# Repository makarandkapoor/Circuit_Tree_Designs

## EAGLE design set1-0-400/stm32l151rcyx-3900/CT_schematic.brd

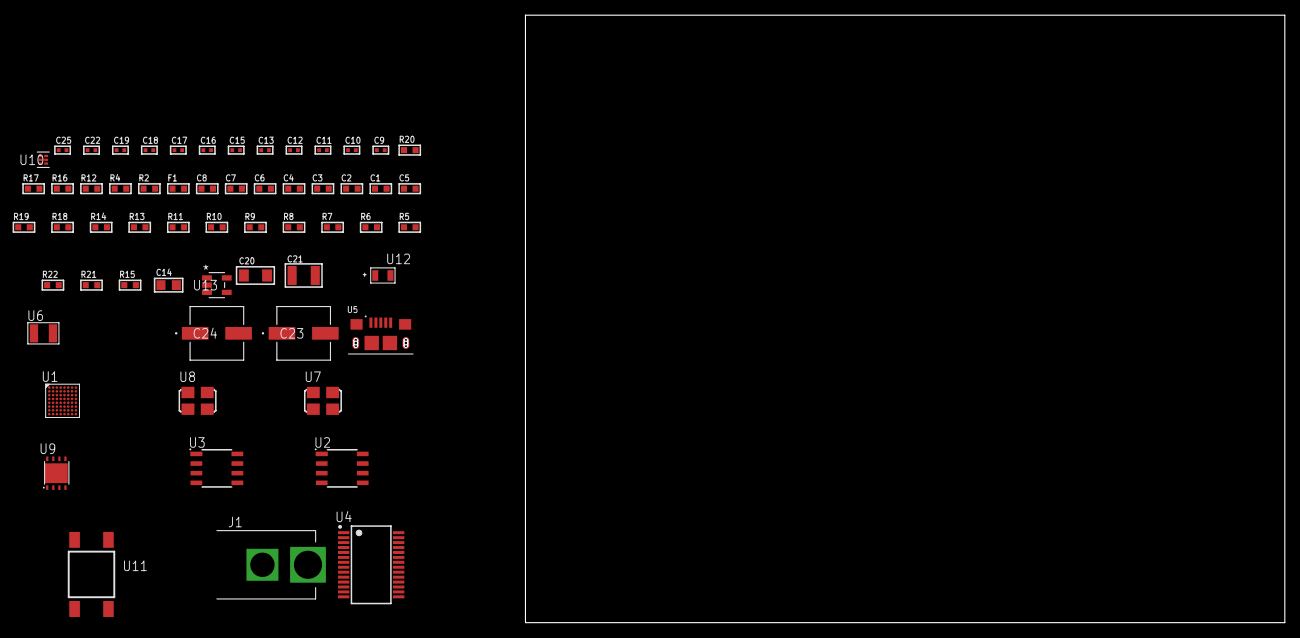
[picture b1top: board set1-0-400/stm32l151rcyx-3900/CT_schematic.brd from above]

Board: 2 copper layers, 122.6 x 80.0 mm, 60 parts (0 on the bottom side), 41 nets, no tracks yet.

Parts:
C1, C2, C3, C4, C6: 1e-07; C0603
C5: 4.7e-06; C0603
C7: 1e-08; C0603
C8: 1e-06; C0603
C9, C10: 1e-11; C0402
C11, C12, C17, C18, C19, C25: 1e-08; C0402
C13, C15, C16, C22: 1e-07; C0402
C14: 4.7e-06; C0805
C20: 1e-05; C1206
C21: 1e-05; C1210
C23, C24: 0.0001; EXV-9H
F1: 240.0; L0603
J1: PJ-037B; PJ-037B_PACKAGE
R2, R17: 1000.0; R0603
R4, R12: 4700.0; R0603
R5, R6, R7, R8, R9, R10, R11, R13, R14, R18, R19: 10000.0; R0603
R15: 100000.0; R0603
R16: 2231.0; R0603
R20: 9100.0; R0603
R21: 680000.0; R0603
R22: 120000.0; R0603
U1: STM32L151RCY6TR; WLCSP64
U2, U3: AT25020B-SSHL-T; SOIC-8
U4: FT232RL-REEL; SSOP-28
U5: 10118193-0001LF; FCI_10118193-0001LF
U6: ABS07-32.768KHZ-7-T
U7: ASFL1-12MHZ-NCS; ASFL1
U8: ASFL1-25MHZ-NCS; ASFL1
U9: LP3878SDX-ADJ/NOPB; WSON-8
U10: TPS3895ADRYR; SON-6
U11: 4-1437565-2; SW_4-1437565-2
U12: Q65110A2395; LGM67K-G1J2-24-Z
U13: nc7sz125m5x; NC7SZ125M5X

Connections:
CLK_CRYSTAL_U1_B7: C9.1, U1.B7, U6.1
CLK_CRYSTAL_U1_B8: C10.1, U1.B8, U6.2
CLK_U1_D8: U1.D8, U8.3
CLK_U4_27: U4.27, U7.3
GND: C1.2, C2.2, C3.2, C4.2, C5.2, C6.2, C7.2, C8.2, C9.2, C10.2, C11.2, C12.2, C13.2, C14.2, C15.2, C16.2, C17.2, C18.2, C19.2, C20.2, C21.2, C22.2, C23.2, C24.2, C25.2, J1.2, R2.2, R5.2, R14.2, R17.2, R20.2, R22.2, U1.A7, U1.B1, U1.E7, U1.F5, U1.H2, U2.4, U3.4, U4.7, U4.18, U4.21, U4.25, U4.26, U5.5, U5.6, U5.7, U5.8, U5.9, U7.2, U8.2, U9.3, U9.PAD, U10.2, U12.C, U13.1, U13.3
NET_U1_A6: R5.1, U1.A6
NET_U1_C6: C6.1, U1.C6
NET_U1_C7: R4.1, U1.C7, U13.4
NET_U1_G8: C7.1, C8.1, F1.1, U1.G8
NET_U1_H8: U11.3, U11.4
NET_U2_3: R6.1, U2.3
NET_U2_7: R8.1, U2.7
NET_U3_3: R9.1, U3.3
NET_U3_7: R11.1, U3.7
NET_U4_14: R13.1, U4.14
NET_U4_17: C15.1, U4.17
NET_U4_19: R14.1, U4.19
NET_U5_1: R12.1, U5.1
NET_U5_2: U4.16, U5.2
NET_U5_3: U4.15, U5.3
NET_U9_1: C19.1, U9.1
NET_U9_6: R16.2, R17.1, U9.6
NET_U9_8: R15.1, U9.8
NET_U10_1: R19.1, R20.1, U10.1
NET_U10_3: R21.2, R22.1, U10.3
NET_U10_4: R18.1, U10.4, U13.2
NET_U11_1: R2.1, U11.1, U11.2
PROC_SPI1_MISO: U1.B4, U2.2
PROC_SPI1_MOSI: U1.A5, U2.5
PROC_SPI1_NSS: R7.1, U1.C3, U2.1
PROC_SPI1_SCK: U1.A4, U2.6
PROC_SPI2_MISO: U1.F2, U3.2
PROC_SPI2_MOSI: U1.F1, U3.5
PROC_SPI2_NSS: R10.1, U1.G2, U3.1
PROC_SPI2_SCK: U1.G1, U3.6
PROC_USART1_CTS: U1.C1, U4.3
PROC_USART1_RTS: U1.C2, U4.11
PROC_USART1_RX: U1.C5, U4.1
PROC_USART1_TX: U1.B5, U4.5
VCC_S1_6V3: C20.1, C23.1, C24.1, J1.1, R15.2, U9.4
VCC_TIER1_3V3: C1.1, C2.1, C3.1, C4.1, C5.1, C11.1, C12.1, C13.1, C14.1, C16.1, C17.1, C18.1, C21.1, C22.1, C25.1, F1.2, R4.2, R6.2, R7.2, R8.2, R9.2, R10.2, R11.2, R13.2, R16.1, R18.2, R19.2, R21.1, U1.A1, U1.A8, U1.G6, U1.H1, U2.8, U3.8, U4.4, U4.20, U7.4, U8.4, U9.5, U10.6, U13.5

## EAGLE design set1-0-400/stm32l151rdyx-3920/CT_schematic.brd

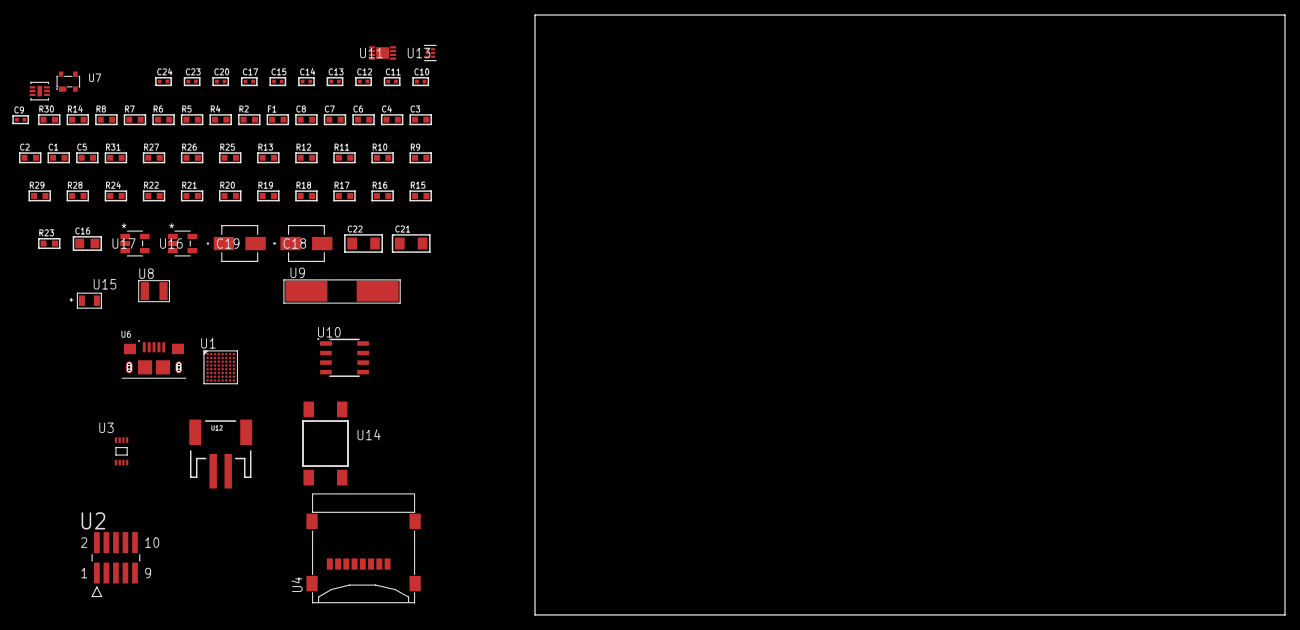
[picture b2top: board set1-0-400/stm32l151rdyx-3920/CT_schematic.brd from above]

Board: 2 copper layers, 71 parts (0 on the bottom side), 40 nets, no tracks yet.

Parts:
C1, C2, C3, C4, C6: 1e-07; C0603
C5: 4.7e-06; C0603
C7: 1e-08; C0603
C8: 1e-06; C0603
C9, C10, C11, C12: 1e-11; C0402
C13, C15, C17, C20: 1e-07; C0402
C14, C23, C24: 1e-08; C0402
C16: 1e-05; C0805
C18: 1e-06; EXV-9B
C19: 2.2e-06; EXV-9B
C21, C22: 1e-05; C1206
F1: 240.0; L0603
R2: 1000.0; R0603
R4: 4700.0; R0603
R5, R6, R7, R8: 2200.0; R0603
R9, R10, R11, R12, R13, R25, R26, R31: 10000.0; R0603
R14: 5.0; R0603
R15, R16, R17, R18, R19, R20, R21, R22, R24: 100000.0; R0603
R23: 101022.32; R0603
R27: 18000.0; R0603
R28: 470000.0; R0603
R29: 120000.0; R0603
R30: 2000.0; R0603
U1: STM32L151RDY6; WLCSP64
U2: FTSH-105-01-L-DV-K; SAMTEC_FTSH-105-01-L-DV-K
U3: 24AA04-I/MC; TDFN-8/6MM
U4: 0472192001; MOLEX_47219-2001
U5: SI7006-A20-IM; DFN-6
U6: 10118193-0001LF; FCI_10118193-0001LF
U7: prtr5v0u2ax; SOT143B
U8: ABS07-32.768KHZ-7-T
U9: ABLS-25.000MHZ-B2F-T
U10: LP2954AIMX/NOPB; LP2954
U11: MCP73831T-2ACI/MC; DFN8_2X3MC
U12: S2B-PH-SM4-TB(LF)(SN); JST-2-SMD
U13: TPS3895ADRYR; SON-6
U14: 4-1437565-2; SW_4-1437565-2
U15: Q65110A2395; LGM67K-G1J2-24-Z
U16, U17: nc7sz125m5x; NC7SZ125M5X

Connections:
CLK_CRYSTAL_U1_B7: C9.1, U1.B7, U8.1
CLK_CRYSTAL_U1_B8: C10.1, U1.B8, U8.2
CLK_CRYSTAL_U1_D7: C11.1, U1.D7, U9.1
CLK_CRYSTAL_U1_D8: C12.1, U1.D8, U9.2
GND: C1.2, C2.2, C3.2, C4.2, C5.2, C6.2, C7.2, C8.2, C9.2, C10.2, C11.2, C12.2, C13.2, C14.2, C15.2, C16.2, C17.2, C18.2, C19.2, C20.2, C21.2, C22.2, C23.2, C24.2, R2.2, R9.2, R13.2, R14.2, R24.2, R27.2, R29.2, R30.2, U1.A7, U1.B1, U1.E7, U1.F5, U1.H2, U2.3, U2.5, U3.4, U3.7, U4.6, U4.G1, U4.G2, U4.G3, U4.G4, U5.2, U5.7, U6.5, U6.6, U6.7, U6.8, U6.9, U7.1, U10.4, U11.6, U11.9, U12.2, U13.2, U15.C, U16.2, U16.3, U17.1, U17.3
INPUT_USBPOWER_5V: C21.1, R31.2, U6.1, U7.4, U11.1, U11.2
NET_U1_A6: R9.1, U1.A6
NET_U1_B5: R5.1, U1.B5, U5.6
NET_U1_B6: R6.1, U1.B6, U5.1
NET_U1_C6: C6.1, U1.C6
NET_U1_C7: R4.1, U1.C7, U17.4
NET_U1_F3: R8.1, U1.F3, U3.5
NET_U1_G3: R7.1, U1.G3, U3.6
NET_U1_G8: C7.1, C8.1, F1.1, U1.G8
NET_U1_H8: U14.3, U14.4
NET_U2_9: R14.1, U2.9
NET_U10_3: R22.1, U10.3
NET_U10_5: R21.1, U10.5
NET_U10_7: R23.2, R24.1, U10.7
NET_U11_5: R31.1, U11.5
NET_U11_8: R30.1, U11.8
NET_U13_1: R26.1, R27.1, U13.1
NET_U13_3: R28.2, R29.1, U13.3
NET_U13_4: R25.1, U13.4, U16.4, U17.2
NET_U14_1: R2.1, U14.1, U14.2
PROC_SDIO_CK: R16.1, U1.C4, U4.5
PROC_SDIO_CMD: R15.1, U1.A3, U4.3
PROC_SDIO_D0: R17.1, U1.E3, U4.7
PROC_SDIO_D1: R18.1, U1.D1, U4.8
PROC_SDIO_D2: R19.1, U1.A2, U4.1
PROC_SDIO_D3: R20.1, U1.B3, U4.2
PROC_SYS_JTCK_SWCLK: R13.1, U1.B2, U2.4
PROC_SYS_JTDI: R11.1, U1.C3, U2.8
PROC_SYS_JTDO_TRACESWO: U1.A4, U2.6
PROC_SYS_JTMS_SWDIO: R12.1, U1.D4, U2.2
PROC_USB_DM: U1.C1, U6.2, U7.3
PROC_USB_DP: U1.C2, U6.3, U7.2
RST_OUT_U2_JTAG_RST_B: R10.1, U2.10, U16.1
VCC_S1_3V7: C18.1, C22.1, R22.2, U10.8, U11.3, U11.4, U12.1
VCC_TIER1_2V5: C1.1, C2.1, C3.1, C4.1, C5.1, C13.1, C14.1, C15.1, C16.1, C17.1, C19.1, C20.1, C23.1, C24.1, F1.2, R4.2, R5.2, R6.2, R7.2, R8.2, R10.2, R11.2, R12.2, R15.2, R16.2, R17.2, R18.2, R19.2, R20.2, R21.2, R23.1, R25.2, R26.2, R28.1, U1.A1, U1.A8, U1.G6, U1.H1, U2.1, U3.8, U4.4, U5.5, U10.1, U13.6, U16.5, U17.5

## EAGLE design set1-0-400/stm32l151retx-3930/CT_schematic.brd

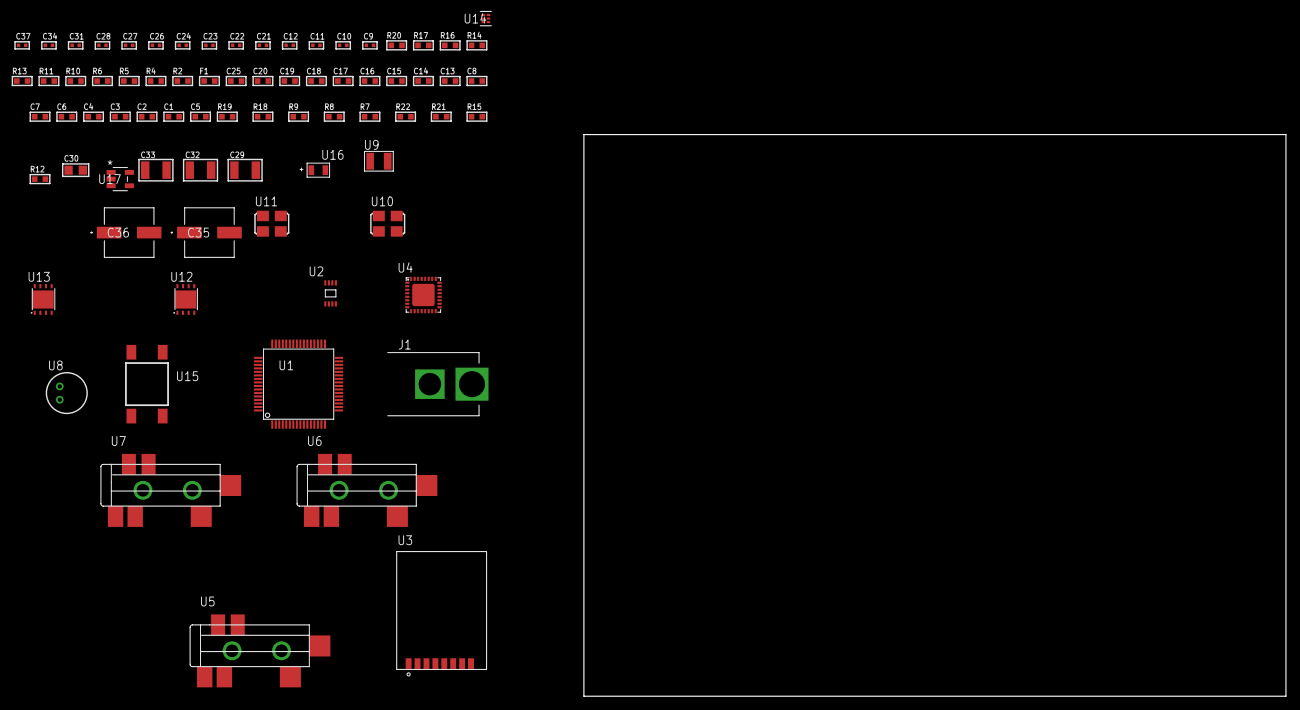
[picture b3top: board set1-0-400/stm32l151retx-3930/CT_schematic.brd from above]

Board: 2 copper layers, 100.0 x 80.0 mm, 76 parts (0 on the bottom side), 46 nets, no tracks yet.

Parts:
C1, C2, C3, C4, C6: 1e-07; C0603
C5: 4.7e-06; C0603
C7: 1e-08; C0603
C8, C13, C14, C15, C16, C17, C18, C19, C20, C25: 1e-06; C0603
C9, C10: 1e-11; C0402
C11, C26, C27, C28, C31, C37: 1e-08; C0402
C12, C21, C22, C23, C24, C34: 1e-07; C0402
C29, C32, C33: 1e-05; C1210
C30: 1e-05; C0805
C35, C36: 0.0001; EXV-9H
F1: 240.0; L0603
J1: PJ-037B; PJ-037B_PACKAGE
R2, R14, R17: 1000.0; R0603
R4: 4700.0; R0603
R5, R6: 2200.0; R0603
R7, R8, R9, R18, R19: 10000.0; R0603
R10, R11: 1270.0; R0603
R12, R15: 100000.0; R0603
R13: 200.0; R0603
R16: 2231.0; R0603
R20: 9100.0; R0603
R21: 680000.0; R0603
R22: 120000.0; R0603
U1: STM32L151RET6; LQFP64
U2: 24AA04-I/MC; TDFN-8/6MM
U3: RFM75-S
U4: SGTL5000XNAA3; QFN-32
U5, U6, U7: SJ-43515TS-SMT-TR
U8: WM-64PCT; WM-64PC
U9: ABS07-32.768KHZ-7-T
U10: ASFL-24.57MHZ-NCS; ASFL1
U11: ASFL1-25MHZ-NCS; ASFL1
U12, U13: LP3878SDX-ADJ/NOPB; WSON-8
U14: TPS3895ADRYR; SON-6
U15: 4-1437565-2; SW_4-1437565-2
U16: Q65110A2395; LGM67K-G1J2-24-Z
U17: nc7sz125m5x; NC7SZ125M5X

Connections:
CLK_CRYSTAL_U1_3: C9.1, U1.3, U9.1
CLK_CRYSTAL_U1_4: C10.1, U1.4, U9.2
CLK_U1_5: U1.5, U11.3
CLK_U4_21: U4.21, U10.3
GND: C1.2, C2.2, C3.2, C4.2, C5.2, C6.2, C7.2, C8.2, C9.2, C10.2, C11.2, C12.2, C13.2, C21.2, C22.2, C23.2, C24.2, C25.2, C26.2, C27.2, C28.2, C29.2, C30.2, C31.2, C32.2, C33.2, C34.2, C35.2, C36.2, C37.2, J1.2, R2.2, R7.2, R11.2, R14.2, R17.2, R20.2, R22.2, U1.12, U1.18, U1.31, U1.47, U1.63, U2.4, U3.1, U4.1, U4.3, U4.7, U4.EXP, U6.1, U7.1, U8.2, U10.2, U11.2, U12.3, U12.PAD, U13.3, U13.PAD, U14.2, U16.C, U17.1, U17.3
NET_U1_1: C6.1, U1.1
NET_U1_7: R4.1, U1.7, U17.4
NET_U1_13: C7.1, C8.1, F1.1, U1.13
NET_U1_58: R5.1, U1.58, U2.6
NET_U1_59: R6.1, U1.59, U2.5
NET_U1_60: R7.1, U1.60
NET_U1_62: U15.3, U15.4
NET_U3_3: R8.1, U3.3
NET_U4_10: C24.1, U4.10
NET_U4_29: R10.1, U4.29
NET_U4_31: R11.1, U4.31
NET_U5_1: U4.4, U5.1
NET_U5_2: U4.2, U5.2
NET_U5_5: U4.6, U5.5
NET_U6_2: C15.1, U6.2
NET_U6_5: C14.1, U6.5
NET_U7_2: C17.1, C18.1, U7.2
NET_U7_5: C16.1, U7.5
NET_U7_13: C17.2, C18.2
NET_U8_1: C19.1, C20.1, C25.1, U4.16, U8.1
NET_U8_15: C19.2, C20.2
NET_U12_1: C28.1, U12.1
NET_U12_6: R13.2, R14.1, U12.6
NET_U12_8: R12.1, U12.8
NET_U13_1: C31.1, U13.1
NET_U13_6: R16.2, R17.1, U13.6
NET_U13_8: R15.1, U13.8
NET_U14_1: R19.1, R20.1, U14.1
NET_U14_3: R21.2, R22.1, U14.3
NET_U14_4: R18.1, U14.4, U17.2
NET_U15_1: R2.1, U15.1, U15.2
PROC_I2S2_CK: U1.34, U4.24
PROC_I2S2_SD: U1.36, U4.26
PROC_I2S2_WS: U1.33, U4.23
PROC_SPI1_MISO: U1.22, U3.7
PROC_SPI1_MOSI: U1.23, U3.6
PROC_SPI1_NSS: R9.1, U1.20, U3.4
PROC_SPI1_SCK: U1.21, U3.5
VCC_S1_15V7: C29.1, C32.1, C35.1, C36.1, J1.1, R12.2, R15.2, U12.4, U13.4
VCC_TIER1_1V2: C21.1, C30.1, R13.1, U4.30, U12.5
VCC_TIER1_3V3: C1.1, C2.1, C3.1, C4.1, C5.1, C11.1, C12.1, C13.1, C22.1, C23.1, C26.1, C27.1, C33.1, C34.1, C37.1, F1.2, R4.2, R5.2, R6.2, R8.2, R9.2, R10.2, R16.1, R18.2, R19.2, R21.1, U1.19, U1.32, U1.48, U1.64, U2.7, U2.8, U3.2, U4.5, U4.20, U10.4, U11.4, U13.5, U14.6, U17.5

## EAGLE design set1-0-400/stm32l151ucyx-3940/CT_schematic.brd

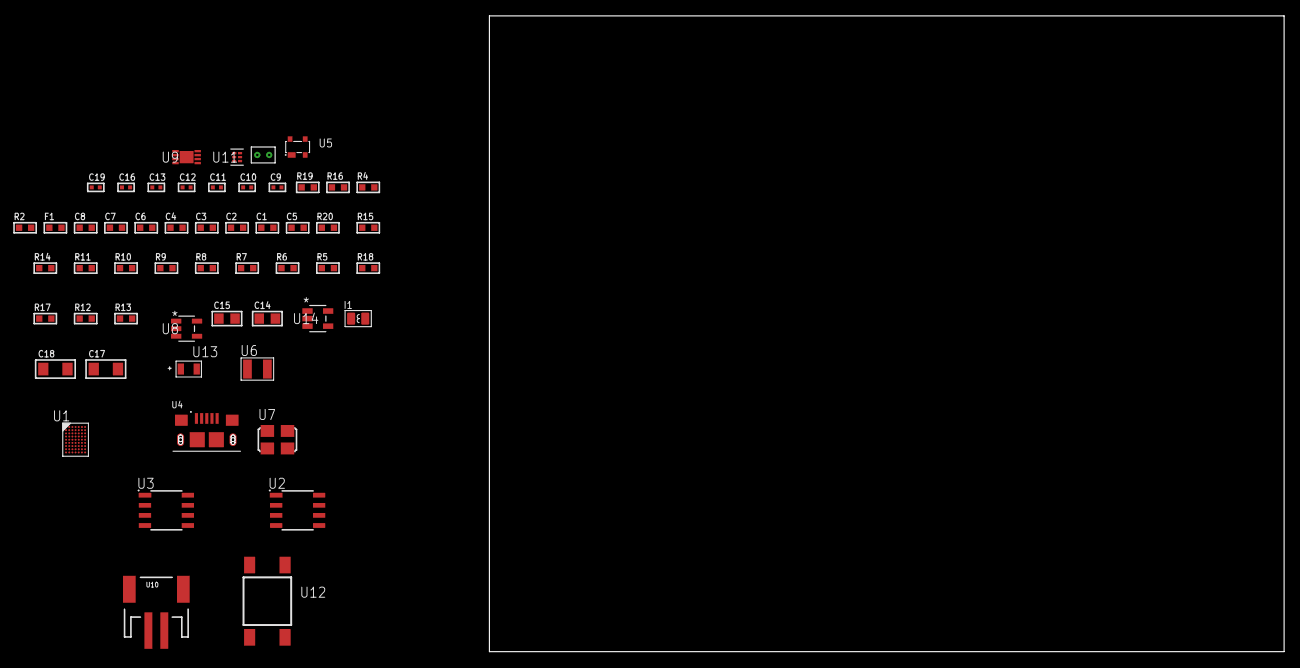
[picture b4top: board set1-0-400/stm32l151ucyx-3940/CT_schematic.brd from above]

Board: 2 copper layers, 54 parts (0 on the bottom side), 36 nets, no tracks yet.

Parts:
C1, C2, C3, C4, C6: 1e-07; C0603
C5: 4.7e-06; C0603
C7: 1e-08; C0603
C8: 1e-06; C0603
C9, C10: 1e-11; C0402
C11, C12, C13, C19: 1e-08; C0402
C14, C15: 1e-05; C0805
C16: 1e-07; C0402
C17, C18: 1e-05; C1206
F1: 240.0; L0603
I1: 3.3e-06; L0806
R2: 1000.0; R0603
R4: 4700.0; R0603
R5, R6, R7, R8, R9, R10, R11, R14, R15, R20: 10000.0; R0603
R12: 220000.0; R0603
R13: 1000000.0; R0603
R16: 9100.0; R0603
R17: 680000.0; R0603
R18: 120000.0; R0603
R19: 2000.0; R0603
U1: STM32L151UCY6; WLCSP63
U2: AT25040B-SSHL-T; SOIC-8
U3: AT25320B-SSHL-T; SOIC-8
U4: 10118193-0001LF; FCI_10118193-0001LF
U5: prtr5v0u2ax; SOT143B
U6: ABS07-32.768KHZ-7-T
U7: ASFL1-25MHZ-NCS; ASFL1
U8: ltc3406es5; TSOT-23-5
U9: MCP73831T-2ACI/MC; DFN8_2X3MC
U10: S2B-PH-SM4-TB(LF)(SN); JST-2-SMD
U11: TPS3895ADRYR; SON-6
U12: 4-1437565-2; SW_4-1437565-2
U13: Q65110A2395; LGM67K-G1J2-24-Z
U14: nc7sz125m5x; NC7SZ125M5X
U15: Dummy; DUMMY_PACKAGE_118

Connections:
CLK_CRYSTAL_U1_D6: C9.1, U1.D6, U6.1
CLK_CRYSTAL_U1_D7: C10.1, U1.D7, U6.2
CLK_U1_F6: U1.F6, U7.3
GND: C1.2, C2.2, C3.2, C4.2, C5.2, C6.2, C7.2, C8.2, C9.2, C10.2, C11.2, C12.2, C13.2, C14.2, C15.1, C15.2, C16.2, C17.2, C18.2, C19.2, R2.2, R5.2, R12.2, R16.2, R18.2, R19.2, U1.A1, U1.A7, U1.F5, U1.H5, U1.J1, U2.4, U3.4, U4.5, U4.6, U4.7, U4.8, U4.9, U5.1, U7.2, U8.2, U9.6, U9.9, U10.2, U11.2, U13.C, U14.1, U14.3, U15.1
INPUT_USBPOWER_5V: C17.1, R20.2, U4.1, U5.4, U9.1, U9.2
NET_U1_A6: R5.1, U1.A6
NET_U1_C7: C6.1, U1.C7
NET_U1_E7: R4.1, U1.E7, U14.4
NET_U1_H7: C7.1, C8.1, F1.1, U1.H7
NET_U1_J7: U12.3, U12.4
NET_U2_3: R6.1, U2.3
NET_U2_7: R8.1, U2.7
NET_U3_3: R9.1, U3.3
NET_U3_7: R11.1, U3.7
NET_U8_3: I1.1, U8.3
NET_U8_5: R12.1, R13.1, U8.5
NET_U8_ATNET_3: I1.2, R13.2
NET_U9_5: R20.1, U9.5
NET_U9_8: R19.1, U9.8
NET_U11_1: R15.1, R16.1, U11.1
NET_U11_3: R17.2, R18.1, U11.3
NET_U11_4: R14.1, U11.4, U14.2
NET_U12_1: R2.1, U12.1, U12.2
PROC_DAC_OUT2: U1.H4, U15.2
PROC_SPI1_MISO: U1.D4, U3.2
PROC_SPI1_MOSI: U1.A5, U3.5
PROC_SPI1_NSS: R10.1, U1.A2, U3.1
PROC_SPI1_SCK: U1.C4, U3.6
PROC_SPI2_MISO: U1.F3, U2.2
PROC_SPI2_MOSI: U1.F2, U2.5
PROC_SPI2_NSS: R7.1, U1.G2, U2.1
PROC_SPI2_SCK: U1.G1, U2.6
PROC_USB_DM: U1.B1, U4.2, U5.3
PROC_USB_DP: U1.D3, U4.3, U5.2
VCC_S1_3V7: C14.1, C18.1, U8.4, U9.3, U9.4, U10.1
VCC_TIER1_3V3: C1.1, C2.1, C3.1, C4.1, C5.1, C11.1, C12.1, C13.1, C15.2, C16.1, C19.1, F1.2, I1.2, R4.2, R6.2, R7.2, R8.2, R9.2, R10.2, R11.2, R13.2, R14.2, R15.2, R17.1, U1.B2, U1.B7, U1.H1, U2.8, U3.8, U7.4, U11.6, U14.5

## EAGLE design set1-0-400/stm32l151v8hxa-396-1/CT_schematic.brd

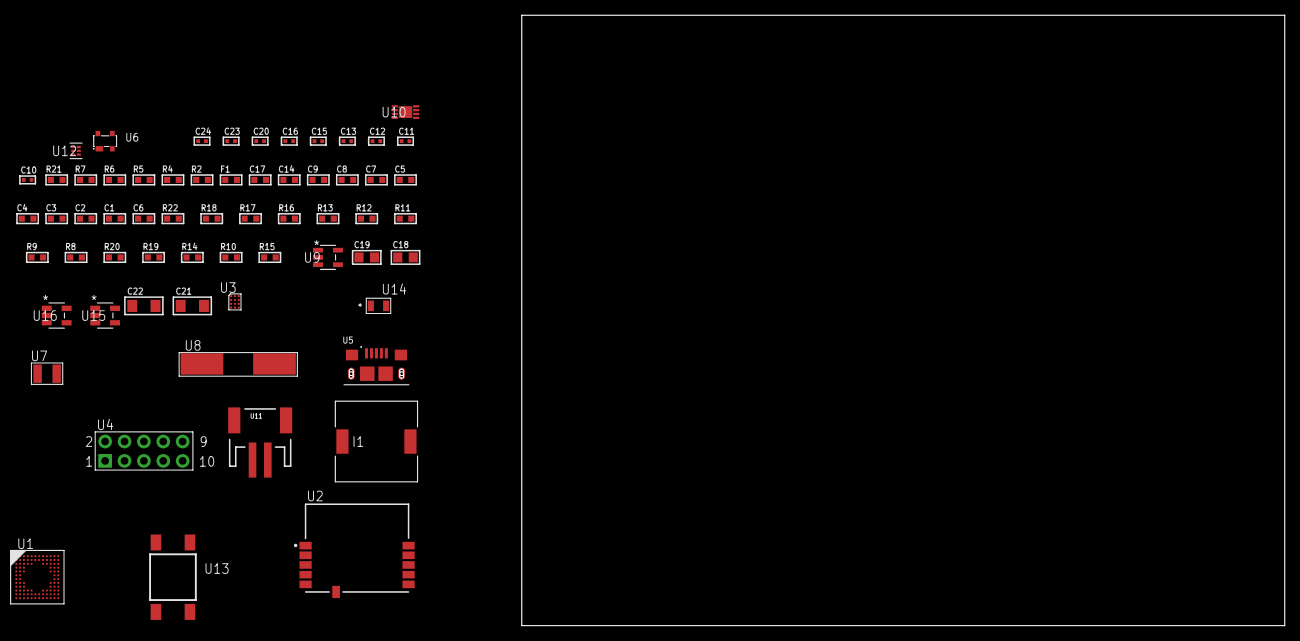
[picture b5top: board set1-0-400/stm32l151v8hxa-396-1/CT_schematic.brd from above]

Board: 2 copper layers, 122.6 x 80.0 mm, 62 parts (0 on the bottom side), 38 nets, no tracks yet.

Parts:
C1, C2, C3, C4, C5, C7: 1e-07; C0603
C6: 4.7e-06; C0603
C8: 1e-08; C0603
C9, C14, C17: 1e-06; C0603
C10, C11, C12, C13: 1e-11; C0402
C15, C16, C20: 1e-07; C0402
C18, C19: 1e-05; C0805
C21, C22: 1e-05; C1206
C23, C24: 1e-08; C0402
F1: 240.0; L0603
I1: 7e-06; DR1040
R2: 1000.0; R0603
R4, R5: 4700.0; R0603
R6, R7: 2200.0; R0603
R8, R9, R12, R13, R16, R17, R22: 10000.0; R0603
R10: 100000.0; R0603
R11: 47000.0; R0603
R14: 490000.0; R0603
R15: 1000000.0; R0603
R18: 82000.0; R0603
R19: 300000.0; R0603
R20: 120000.0; R0603
R21: 2000.0; R0603
U1: STM32L151V8H6A; UFBGA100
U2: SPBTLE-RF; XCVR_SPBTLE-RF
U3: TSC2014IYZGT
U4: HTSS-105-01-G-D
U5: 10118193-0001LF; FCI_10118193-0001LF
U6: prtr5v0u2ax; SOT143B
U7: ABS07-32.768KHZ-7-T
U8: ABLS-25.000MHZ-B2F-T
U9: ltc3406es5; TSOT-23-5
U10: MCP73831T-2ACI/MC; DFN8_2X3MC
U11: S2B-PH-SM4-TB(LF)(SN); JST-2-SMD
U12: TPS3895ADRYR; SON-6
U13: 4-1437565-2; SW_4-1437565-2
U14: Q65110A2395; LGM67K-G1J2-24-Z
U15, U16: nc7sz125m5x; NC7SZ125M5X

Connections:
CLK_CRYSTAL_U1_D1: C10.1, U1.D1, U7.1
CLK_CRYSTAL_U1_E1: C11.1, U1.E1, U7.2
CLK_CRYSTAL_U1_F1: C12.1, U1.F1, U8.1
CLK_CRYSTAL_U1_G1: C13.1, U1.G1, U8.2
GND: C1.2, C2.2, C3.2, C4.2, C5.2, C6.2, C7.2, C8.2, C9.2, C10.2, C11.2, C12.2, C13.2, C14.2, C15.2, C16.2, C17.2, C18.2, C19.1, C19.2, C20.2, C21.2, C22.2, C23.2, C24.2, R2.2, R8.2, R10.2, R11.2, R14.2, R18.2, R20.2, R21.2, U1.D3, U1.E3, U1.F2, U1.F11, U1.F12, U1.J1, U1.K1, U2.6, U3.B2, U3.D2, U4.9, U5.5, U5.6, U5.7, U5.8, U5.9, U6.1, U9.2, U10.6, U10.9, U11.2, U12.2, U14.C, U15.1, U15.3, U16.1, U16.3
INPUT_USBPOWER_5V: C21.1, R22.2, U5.1, U6.4, U10.1, U10.2
NET_U1_A3: R6.1, U1.A3, U3.D1
NET_U1_A4: R8.1, U1.A4
NET_U1_B3: R7.1, U1.B3, U3.C1
NET_U1_E2: C7.1, U1.E2
NET_U1_H2: R5.1, U1.H2, U16.4
NET_U1_M1: C8.1, C9.1, F1.1, U1.L1, U1.M1
NET_U1_M12: U13.3, U13.4
NET_U2_11: R4.1, U2.11, U15.4
NET_U3_B1: R13.1, U3.B1
NET_U3_C2: R12.1, U3.C2
NET_U4_3: U3.B3, U4.3
NET_U4_4: U3.D3, U4.4
NET_U4_5: U3.A3, U4.5
NET_U4_6: U3.C3, U4.6
NET_U9_3: I1.1, U9.3
NET_U9_5: R14.1, R15.1, U9.5
NET_U9_ATNET_3: I1.2, R15.2
NET_U10_5: R22.1, U10.5
NET_U10_8: R21.1, U10.8
NET_U12_1: R17.1, R18.1, U12.1
NET_U12_3: R19.2, R20.1, U12.3
NET_U12_4: R16.1, U12.4, U15.2, U16.2
NET_U13_1: R2.1, U13.1, U13.2
PROC_GPIO_TO_U2_SPI_IRQ: R11.1, U1.A1, U2.4
PROC_SPI1_MISO: U1.A7, U2.8
PROC_SPI1_MOSI: U1.C5, U2.9
PROC_SPI1_NSS: R9.1, U1.A9, U2.10
PROC_SPI1_SCK: R10.1, U1.A8, U2.7
PROC_USB_DM: U1.B12, U5.2, U6.3
PROC_USB_DP: U1.A12, U5.3, U6.2
VCC_S1_3V7: C18.1, C22.1, U9.4, U10.3, U10.4, U11.1
VCC_TIER1_1V8: C1.1, C2.1, C3.1, C4.1, C5.1, C6.1, C14.1, C15.1, C16.1, C17.1, C19.2, C20.1, C23.1, C24.1, F1.2, I1.2, R4.2, R5.2, R6.2, R7.2, R9.2, R12.2, R13.2, R15.2, R16.2, R17.2, R19.1, U1.C4, U1.G2, U1.G11, U1.G12, U1.H3, U2.5, U3.A2, U12.6, U15.5, U16.5

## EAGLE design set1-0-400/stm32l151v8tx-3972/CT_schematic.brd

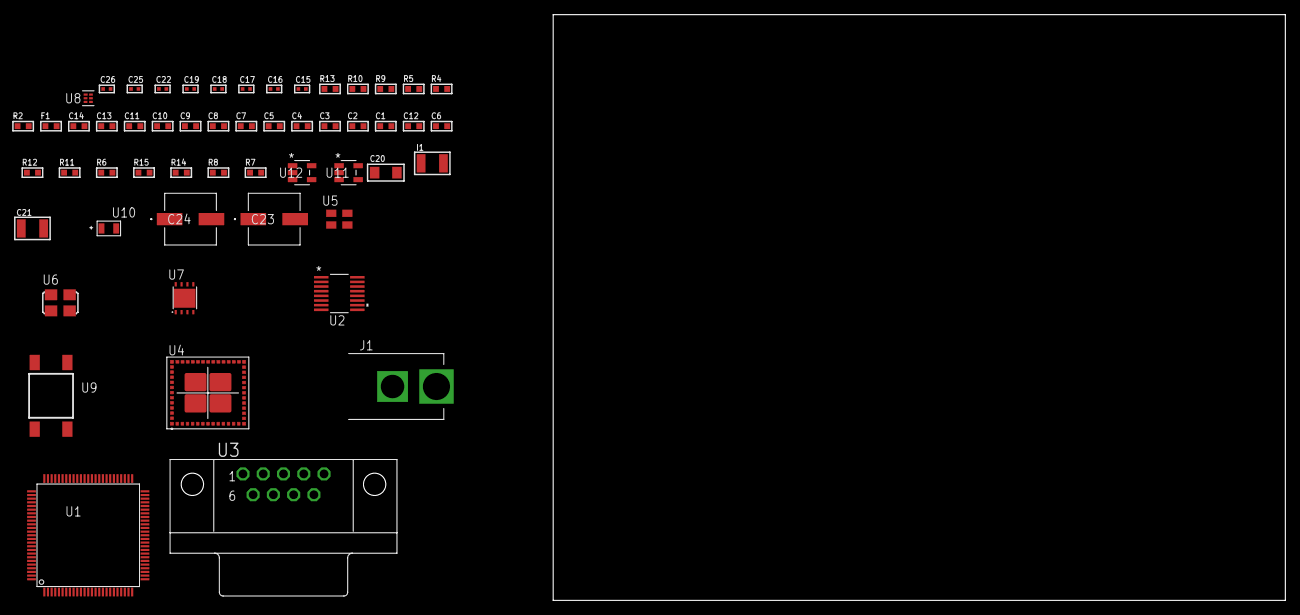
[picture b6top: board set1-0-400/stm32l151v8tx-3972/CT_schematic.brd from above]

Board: 2 copper layers, 100.0 x 80.0 mm, 54 parts (0 on the bottom side), 31 nets, no tracks yet.

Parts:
C1, C2, C3, C4, C5, C7: 1e-07; C0603
C6: 4.7e-06; C0603
C8: 1e-08; C0603
C9, C10, C11, C13, C14: 1e-06; C0603
C12: 2.2e-07; C0603
C15, C16, C22: 1e-07; C0402
C17, C18, C19, C25, C26: 1e-08; C0402
C20: 1e-05; C1206
C21: 1e-05; C1210
C23, C24: 0.0001; EXV-9H
F1: 240.0; L0603
I1: 1e-05; L1210
J1: PJ-037B; PJ-037B_PACKAGE
R2, R10: 1000.0; R0603
R4, R5: 4700.0; R0603
R6, R11, R12: 10000.0; R0603
R7, R8: 100000.0; R0603
R9: 2231.0; R0603
R13: 9100.0; R0603
R14: 680000.0; R0603
R15: 120000.0; R0603
U1: STM32L151V8T6; LQFP100
U2: LTC2804CGN-1#PBF; SSOP-16
U3: 182-009-113R531; 182-009-MALE
U4: MBH7BLZ02-109004
U5: ASEK-32.768KHz-ECST; ASEK
U6: ASFL1-25MHZ-NCS; ASFL1
U7: LP3878SDX-ADJ/NOPB; WSON-8
U8: TPS3895ADRYR; SON-6
U9: 4-1437565-2; SW_4-1437565-2
U10: Q65110A2395; LGM67K-G1J2-24-Z
U11, U12: nc7sz125m5x; NC7SZ125M5X

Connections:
CLK_U1_8: U1.8, U5.3
CLK_U1_12: U1.12, U6.3
GND: C1.2, C2.2, C3.2, C4.2, C5.2, C6.2, C7.2, C8.2, C9.2, C10.2, C11.2, C13.2, C14.2, C15.2, C16.2, C17.2, C18.2, C19.2, C20.2, C21.2, C22.2, C23.2, C24.2, C25.2, C26.2, J1.2, R2.2, R6.2, R10.2, R13.2, R15.2, U1.10, U1.19, U1.20, U1.27, U1.49, U1.74, U1.99, U2.8, U3.5, U4.1, U4.3, U4.15, U4.27, U4.29, U4.41, U4.42, U4.43, U4.44, U4.45, U4.46, U4.47, U4.48, U4.49, U4.50, U4.52, U4.53, U4.54, U4.55, U4.56, U5.2, U6.2, U7.3, U7.PAD, U8.2, U10.C, U11.1, U11.3, U12.1, U12.3
NET_U1_6: C7.1, U1.6
NET_U1_14: R5.1, U1.14, U12.4
NET_U1_22: C8.1, C9.1, F1.1, U1.21, U1.22
NET_U1_94: R6.1, U1.94
NET_U1_98: U9.3, U9.4
NET_U2_6: C10.1, U2.6
NET_U2_7: C12.1, I1.2, U2.7
NET_U2_9: C11.1, U2.9
NET_U2_10: C12.2, U2.10
NET_U2_11: R7.1, U2.11
NET_U3_2: U2.1, U3.2
NET_U3_3: U2.3, U3.3
NET_U3_7: U2.2, U3.7
NET_U3_8: U2.4, U3.8
NET_U4_39: R4.1, U4.39, U11.4
NET_U7_1: C19.1, U7.1
NET_U7_6: R9.2, R10.1, U7.6
NET_U7_8: R8.1, U7.8
NET_U8_1: R12.1, R13.1, U8.1
NET_U8_3: R14.2, R15.1, U8.3
NET_U8_4: R11.1, U8.4, U11.2, U12.2
NET_U9_1: R2.1, U9.1, U9.2
PROC_USART1_CTS: U1.70, U4.26
PROC_USART1_RTS: U1.71, U4.24
PROC_USART1_RX: U1.69, U4.25
PROC_USART1_TX: U1.68, U4.23
VCC_S1_9V4: C20.1, C23.1, C24.1, J1.1, R8.2, U7.4
VCC_TIER1_3V3: C1.1, C2.1, C3.1, C4.1, C5.1, C6.1, C13.1, C14.1, C15.1, C16.1, C17.1, C18.1, C21.1, C22.1, C25.1, C26.1, F1.2, I1.1, R4.2, R5.2, R7.2, R9.1, R11.2, R12.2, R14.1, U1.11, U1.28, U1.50, U1.75, U1.100, U2.5, U2.12, U4.28, U5.4, U6.4, U7.5, U8.6, U11.5, U12.5

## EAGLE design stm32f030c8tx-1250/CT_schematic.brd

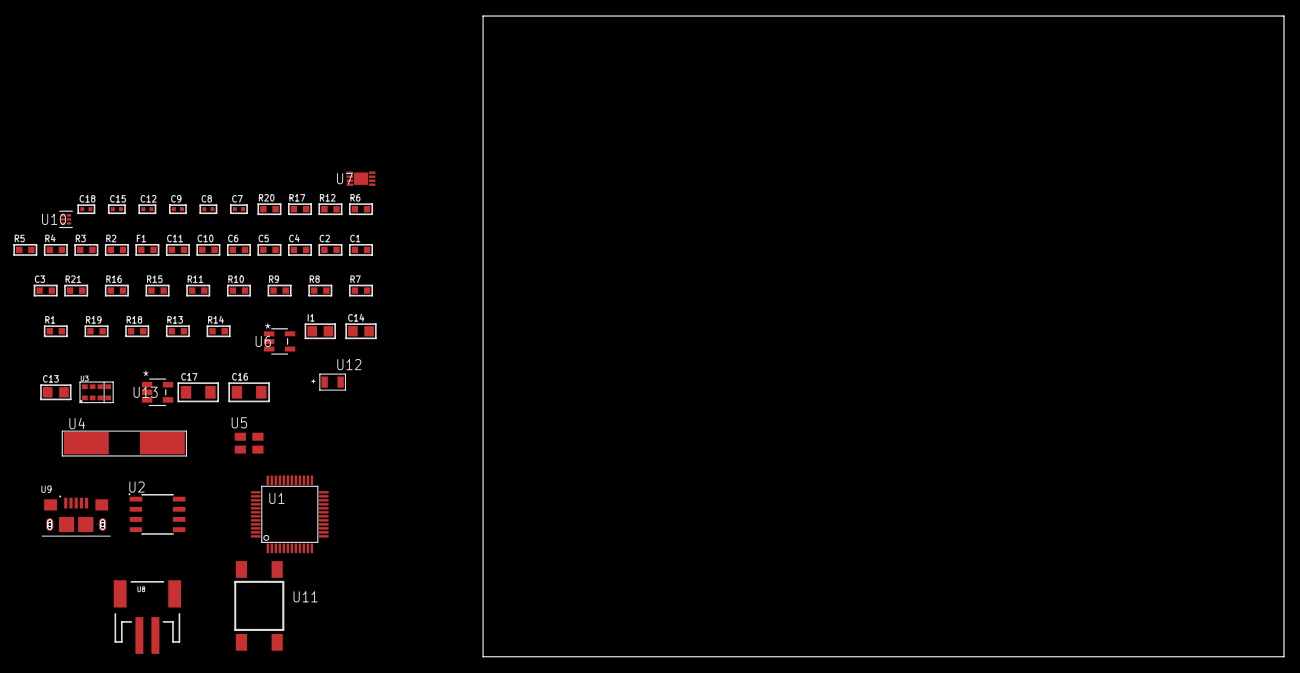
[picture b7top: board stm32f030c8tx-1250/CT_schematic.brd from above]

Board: 2 copper layers, 154.3 x 80.0 mm, 54 parts (0 on the bottom side), 31 nets, no tracks yet.

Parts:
C1, C2, C4: 1e-07; C0603
C3: 4.7e-06; C0603
C5: 1e-08; C0603
C6, C10, C11: 1e-06; C0603
C7, C8: 1e-11; C0402
C9, C12, C18: 1e-08; C0402
C13, C14: 1e-05; C0805
C15: 1e-07; C0402
C16, C17: 1e-05; C1206
F1: 240.0; L0603
I1: 2.2e-06; L0805
R1, R7, R8, R9, R10, R11, R15, R16, R21: 10000.0; R0603
R2: 1000.0; R0603
R3: 1600.5; R0603
R4: 4700.0; R0603
R5, R6: 2200.0; R0603
R12: 22.0; R0603
R13: 220000.0; R0603
R14: 1000000.0; R0603
R17: 9100.0; R0603
R18: 680000.0; R0603
R19: 120000.0; R0603
R20: 2000.0; R0603
U1: STM32F030C8T6; LQFP48
U2: AT25160B-SSHL-T; SOIC-8
U3: TMD27711; SMD-8
U4: ABLS-25.000MHZ-B2F-T
U5: ASEK-32.768KHz-ECST; ASEK
U6: ltc3406es5; TSOT-23-5
U7: MCP73831T-2ACI/MC; DFN8_2X3MC
U8: S2B-PH-SM4-TB(LF)(SN); JST-2-SMD
U9: 10118193-0001LF; FCI_10118193-0001LF
U10: TPS3895ADRYR; SON-6
U11: 4-1437565-2; SW_4-1437565-2
U12: Q65110A2395; LGM67K-G1J2-24-Z
U13: nc7sz125m5x; NC7SZ125M5X

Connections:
CLK_CRYSTAL_U1_5: C7.1, U1.5, U4.1
CLK_CRYSTAL_U1_6: C8.1, U1.6, U4.2
CLK_U1_3: U1.3, U5.3
GND: C1.2, C2.2, C3.2, C4.2, C5.2, C6.2, C7.2, C8.2, C9.2, C10.2, C11.2, C12.2, C13.2, C14.1, C14.2, C15.2, C16.2, C17.2, C18.2, R2.2, R7.2, R13.2, R17.2, R19.2, R20.2, U1.8, U1.23, U1.47, U2.4, U3.3, U5.2, U6.2, U7.6, U7.9, U8.2, U9.5, U9.6, U9.7, U9.8, U9.9, U10.2, U12.C, U13.1, U13.3
INPUT_USBPOWER_5V: C16.1, R21.2, U7.1, U7.2, U9.1
NET_U1_7: R4.1, U1.7, U13.4
NET_U1_9: C5.1, C6.1, F1.1, U1.9
NET_U1_42: R5.1, U1.42, U3.2
NET_U1_43: R6.1, U1.43, U3.8
NET_U1_44: R7.1, U1.44
NET_U1_45: R3.1, U1.45, U12.A
NET_U1_46: R1.1, U1.46, U11.3, U11.4
NET_U2_3: R8.1, U2.3
NET_U2_7: R10.1, U2.7
NET_U3_4: C11.1, R12.1, U3.4
NET_U3_7: R11.1, U3.7
NET_U6_3: I1.1, U6.3
NET_U6_5: R13.1, R14.1, U6.5
NET_U6_ATNET_3: I1.2, R14.2
NET_U7_5: R21.1, U7.5
NET_U7_8: R20.1, U7.8
NET_U10_1: R16.1, R17.1, U10.1
NET_U10_3: R18.2, R19.1, U10.3
NET_U10_4: R15.1, U10.4, U13.2
NET_U11_1: R2.1, U11.1, U11.2
PROC_SPI1_MISO: U1.16, U2.2
PROC_SPI1_MOSI: U1.17, U2.5
PROC_SPI1_NSS: R9.1, U1.14, U2.1
PROC_SPI1_SCK: U1.15, U2.6
VCC_S1_3V7: C13.1, C17.1, U6.4, U7.3, U7.4, U8.1
VCC_TIER1_3V3: C1.1, C2.1, C3.1, C4.1, C9.1, C10.1, C12.1, C14.2, C15.1, C18.1, F1.2, I1.2, R1.2, R3.2, R4.2, R5.2, R6.2, R8.2, R9.2, R10.2, R11.2, R12.2, R14.2, R15.2, R16.2, R18.1, U1.1, U1.24, U1.48, U2.8, U3.1, U5.4, U10.6, U13.5

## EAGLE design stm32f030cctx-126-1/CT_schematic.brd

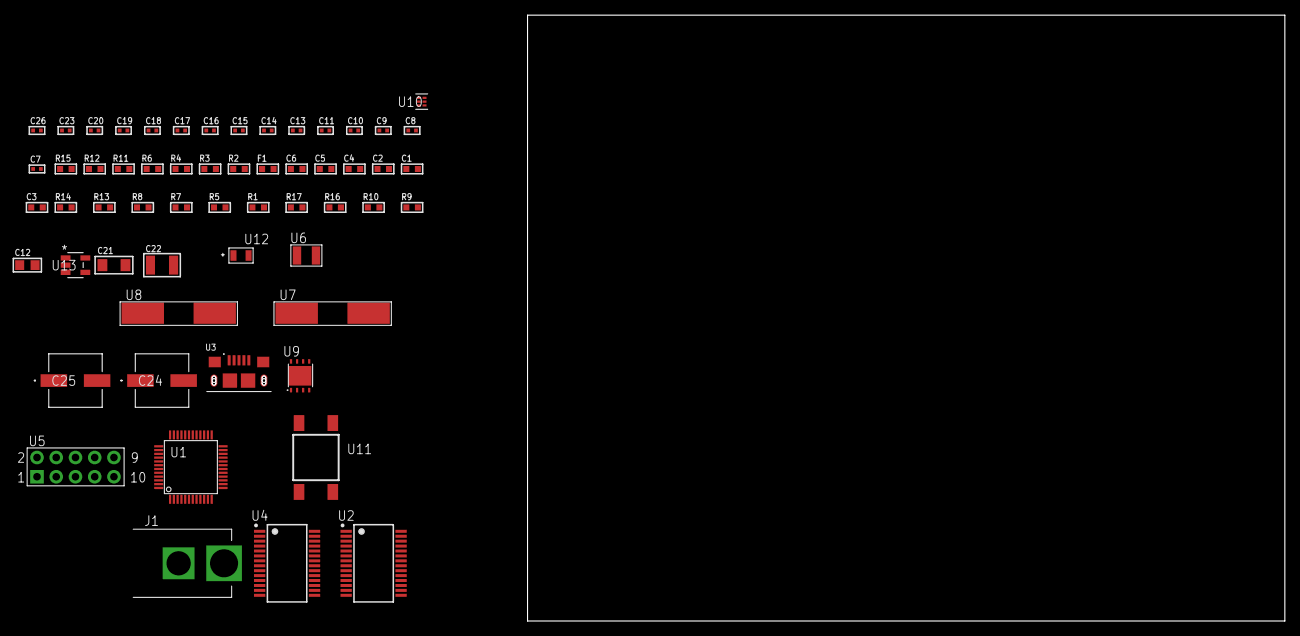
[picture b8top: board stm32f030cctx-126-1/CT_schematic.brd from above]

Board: 2 copper layers, 58 parts (0 on the bottom side), 46 nets, no tracks yet.

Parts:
C1, C2, C4: 1e-07; C0603
C3: 4.7e-06; C0603
C5: 1e-08; C0603
C6: 1e-06; C0603
C7, C8, C9, C10: 1e-11; C0402
C11, C13, C14, C15, C16, C17, C18, C19, C23: 1e-07; C0402
C12: 4.7e-06; C0805
C20, C26: 1e-08; C0402
C21: 1e-05; C1206
C22: 1e-05; C1210
C24, C25: 0.0001; EXV-9H
F1: 240.0; L0603
J1: PJ-037B; PJ-037B_PACKAGE
R1, R5, R7, R8, R13, R14: 10000.0; R0603
R2, R12: 1000.0; R0603
R3: 1600.5; R0603
R4, R6: 4700.0; R0603
R9, R10: 100000.0; R0603
R11: 2231.0; R0603
R15: 9100.0; R0603
R16: 680000.0; R0603
R17: 120000.0; R0603
U1: STM32F030CCT6; LQFP48
U2: FT232RL-REEL; SSOP-28
U3: 10118193-0001LF; FCI_10118193-0001LF
U4: ST3241EBPR; SSOP-28
U5: HTSS-105-01-G-D
U6: ABS07-32.768KHZ-7-T
U7: ABLS-25.000MHZ-B2F-T
U8: ABLS-12.000MHZ-B4-T
U9: LP3878SDX-ADJ/NOPB; WSON-8
U10: TPS3895ADRYR; SON-6
U11: 4-1437565-2; SW_4-1437565-2
U12: Q65110A2395; LGM67K-G1J2-24-Z
U13: nc7sz125m5x; NC7SZ125M5X

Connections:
CLK_CRYSTAL_U1_3: C7.1, U1.3, U6.1
CLK_CRYSTAL_U1_4: C8.1, U1.4, U6.2
CLK_CRYSTAL_U1_5: C9.1, U1.5, U7.1
CLK_CRYSTAL_U1_6: C10.1, U1.6, U7.2
CLK_CRYSTAL_U2_27: U2.27, U8.1
CLK_CRYSTAL_U2_28: U2.28, U8.2
GND: C1.2, C2.2, C3.2, C4.2, C5.2, C6.2, C7.2, C8.2, C9.2, C10.2, C11.2, C12.2, C13.2, C14.2, C15.2, C18.2, C19.2, C20.2, C21.2, C22.2, C23.2, C24.2, C25.2, C26.2, J1.2, R2.2, R5.2, R8.2, R12.2, R15.2, R17.2, U1.8, U1.23, U1.35, U1.47, U2.7, U2.18, U2.21, U2.25, U2.26, U3.5, U3.6, U3.7, U3.8, U3.9, U4.23, U4.25, U5.9, U9.3, U9.PAD, U10.2, U12.C, U13.1, U13.3
NET_U1_7: R4.1, U1.7, U13.4
NET_U1_9: C5.1, C6.1, F1.1, U1.9
NET_U1_44: R5.1, U1.44
NET_U1_45: R3.1, U1.45, U12.A
NET_U1_46: R1.1, U1.46, U11.3, U11.4
NET_U2_14: R7.1, U2.14
NET_U2_17: C13.1, U2.17
NET_U2_19: R8.1, U2.19
NET_U3_1: R6.1, U3.1
NET_U3_2: U2.16, U3.2
NET_U3_3: U2.15, U3.3
NET_U4_1: C17.1, U4.1
NET_U4_2: C17.2, U4.2
NET_U4_3: C19.1, U4.3
NET_U4_22: R9.1, U4.22
NET_U4_24: C16.2, U4.24
NET_U4_27: C18.1, U4.27
NET_U4_28: C16.1, U4.28
NET_U5_3: U4.4, U5.3
NET_U5_4: U4.5, U5.4
NET_U5_5: U4.9, U5.5
NET_U5_6: U4.10, U5.6
NET_U9_1: C20.1, U9.1
NET_U9_6: R11.2, R12.1, U9.6
NET_U9_8: R10.1, U9.8
NET_U10_1: R14.1, R15.1, U10.1
NET_U10_3: R16.2, R17.1, U10.3
NET_U10_4: R13.1, U10.4, U13.2
NET_U11_1: R2.1, U11.1, U11.2
PROC_USART1_CTS: U1.32, U2.3
PROC_USART1_RTS: U1.33, U2.11
PROC_USART1_RX: U1.31, U2.1
PROC_USART1_TX: U1.30, U2.5
PROC_USART2_CTS: U1.10, U4.13
PROC_USART2_RTS: U1.11, U4.18
PROC_USART2_RX: U1.13, U4.19
PROC_USART2_TX: U1.12, U4.14
VCC_S1_10V2: C21.1, C24.1, C25.1, J1.1, R10.2, U9.4
VCC_TIER1_3V3: C1.1, C2.1, C3.1, C4.1, C11.1, C12.1, C14.1, C15.1, C22.1, C23.1, C26.1, F1.2, R1.2, R3.2, R4.2, R7.2, R9.2, R11.1, R13.2, R14.2, R16.1, U1.1, U1.24, U1.36, U1.48, U2.4, U2.20, U4.26, U9.5, U10.6, U13.5
